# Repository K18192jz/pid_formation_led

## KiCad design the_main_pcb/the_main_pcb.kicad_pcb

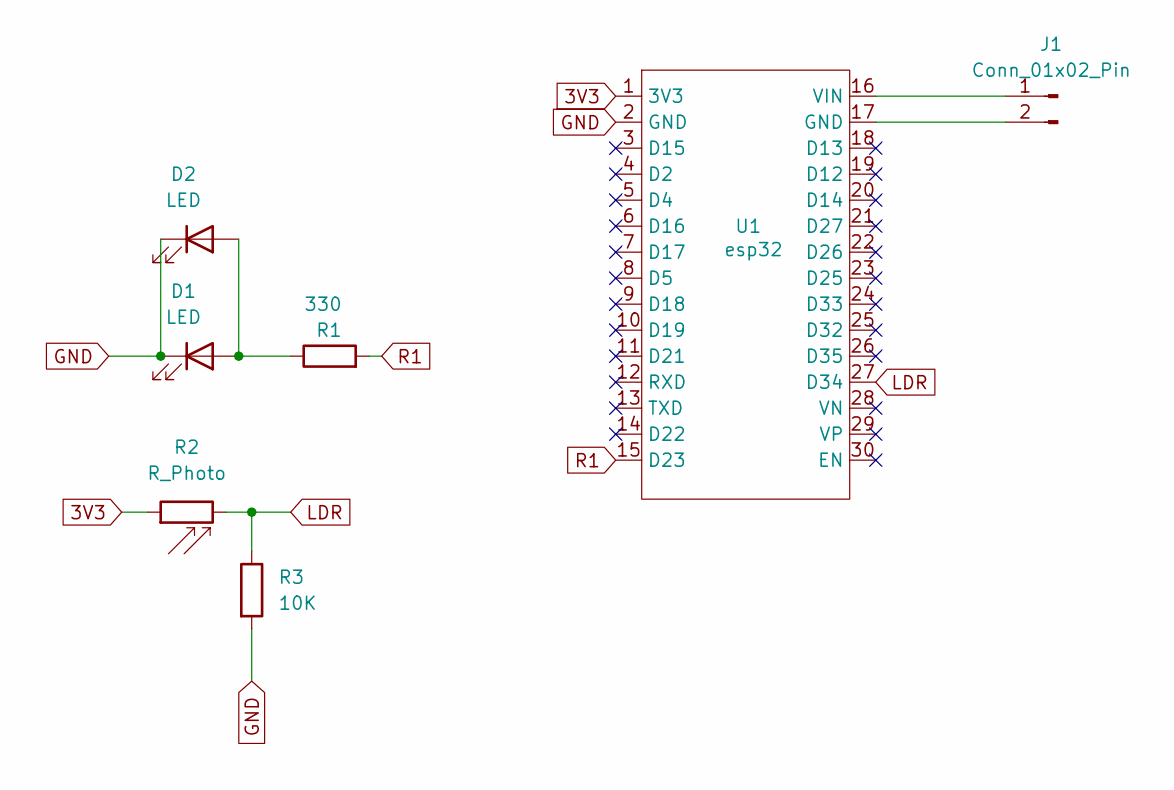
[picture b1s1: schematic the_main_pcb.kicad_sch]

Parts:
D1, D2: LED; LED_D1.8mm_W3.3mm_H2.4mm
J1: Conn_01x02_Pin; PinHeader_1x02_P2.54mm_Vertical
R1: 330; R_Axial_DIN0309_L9.0mm_D3.2mm_P12.70mm_Horizontal
R2: R_Photo; LED_D1.8mm_W3.3mm_H2.4mm
R3: 10K; R_Axial_DIN0309_L9.0mm_D3.2mm_P12.70mm_Horizontal
U1: esp32; Untitled

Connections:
3V3: R2.1, U1.1 (3V3)
GND: D1.1 (K), D2.1 (K), R3.2, U1.2 (GND)
LDR: R2.2, R3.1, U1.27 (D34)
unnamed: D1.2 (A), D2.2 (A), R1.1
unnamed: J1.1, U1.16 (VIN)
unnamed: J1.2, U1.17 (GND)
R1: R1.2, U1.15 (D23)

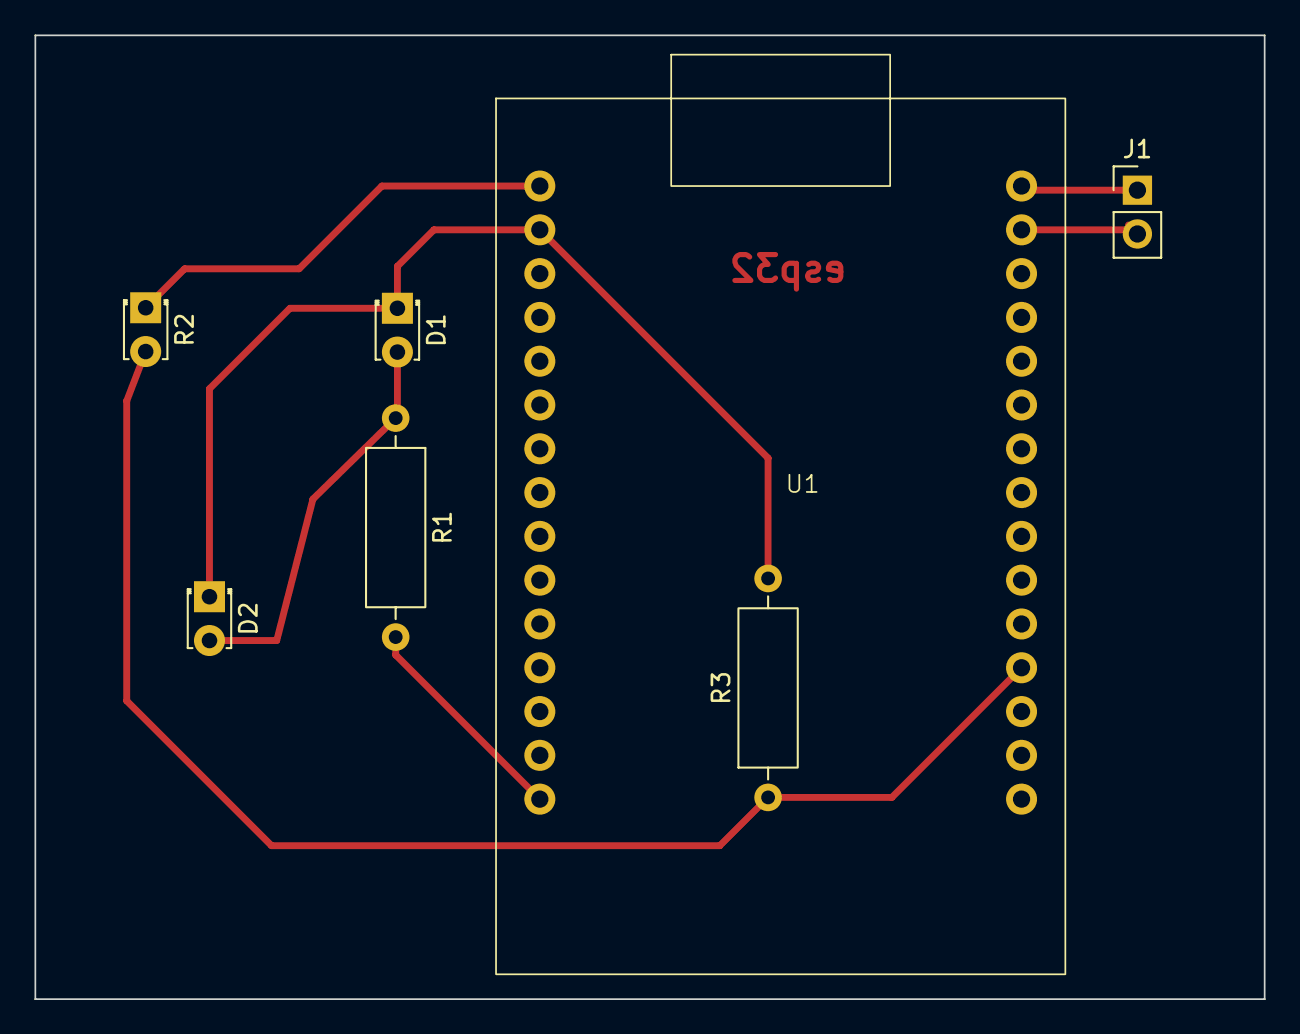
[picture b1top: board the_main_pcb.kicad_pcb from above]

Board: 2 copper layers, 71.3 x 55.9 mm, 7 parts (0 on the bottom side), 7 nets.

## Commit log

2026-02-24 added the code
2026-02-24 start working on the pcb
2026-02-24 done with the esp32 costume pcb
2026-02-25 command throw wifi but the page won update the values
2026-02-25 better filter
2026-02-25 update time
2026-02-25 worked more on the pcb
2026-02-25 start working on the 3D
2026-02-26 matlab simulation
2026-03-05 updated the PCB pdf
2026-03-07 more working on the code
2026-03-10 i added the presentation
